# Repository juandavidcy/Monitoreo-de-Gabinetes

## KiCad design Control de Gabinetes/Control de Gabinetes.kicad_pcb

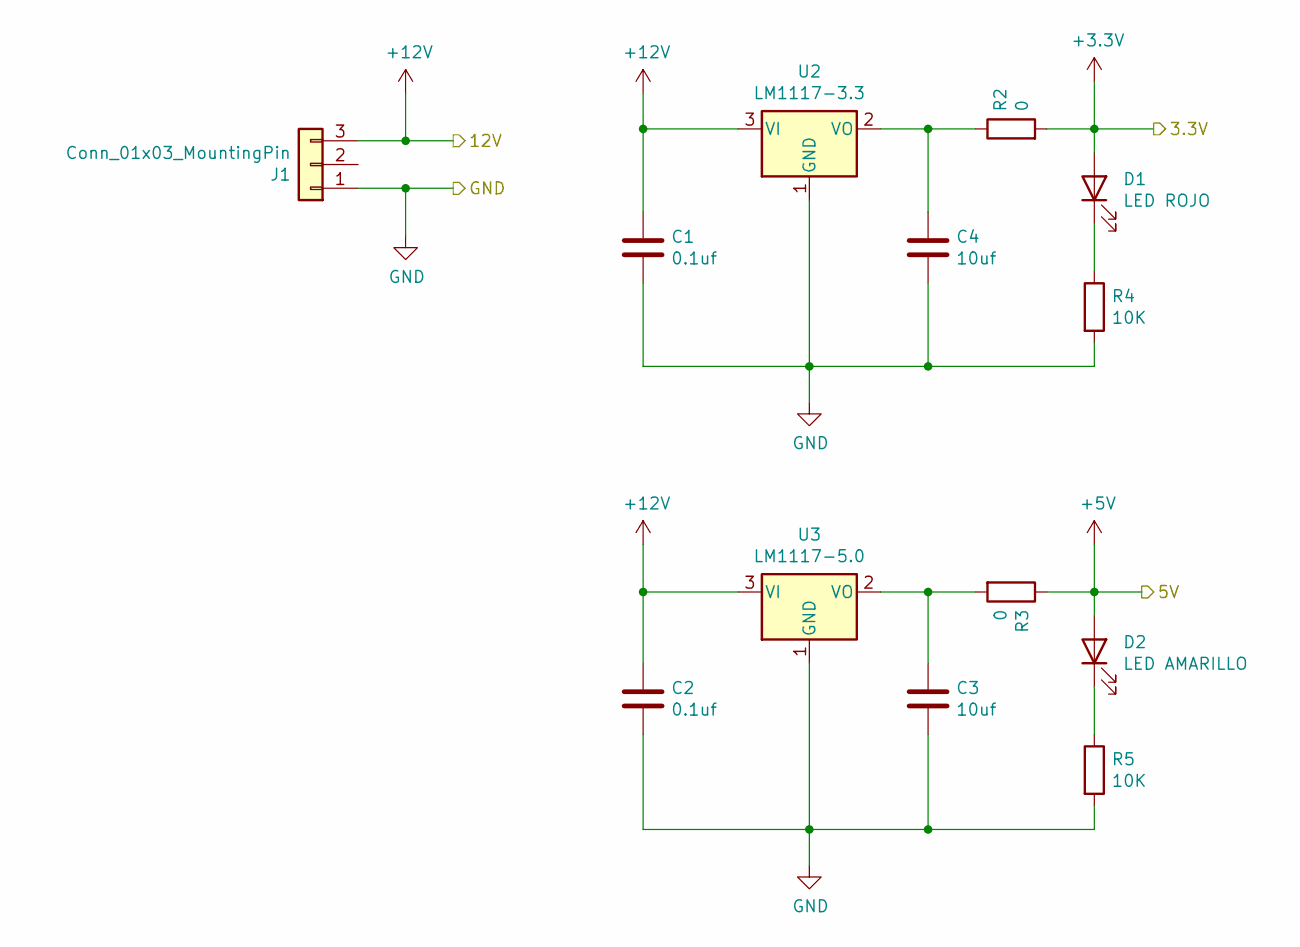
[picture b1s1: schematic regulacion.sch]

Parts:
C1, C2: 0.1uf; C_0805_2012Metric
C3, C4: 10uf; C_0805_2012Metric
D1: LED ROJO; LED_0805_2012Metric
D2: LED AMARILLO; LED_0805_2012Metric
J1: Conn_01x03_MountingPin; Molex_KK-254_AE-6410-03A_1x03_P2.54mm_Vertical
R2, R3: 0; R_0805_2012Metric
R4, R5: 10K; R_0805_2012Metric
U2: LM1117-3.3; SOT-223-3_TabPin2
U3: LM1117-5.0; SOT-223-3_TabPin2

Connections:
+3V3: D1.2 (A), R2.2; also elsewhere on the board
+5V: D2.2 (A), R3.1; also elsewhere on the board
+12V: C1.1, C2.1, J1.3, U2.3 (VI), U3.3 (VI)
GND: C1.2, C2.2, C3.2, C4.2, J1.1, R4.2, R5.2, U2.1 (GND), U3.1 (GND); also elsewhere on the board
unnamed: C3.1, R3.2, U3.2 (VO)
unnamed: C4.1, R2.1, U2.2 (VO)
unnamed: D1.1 (K), R4.1
unnamed: D2.1 (K), R5.1

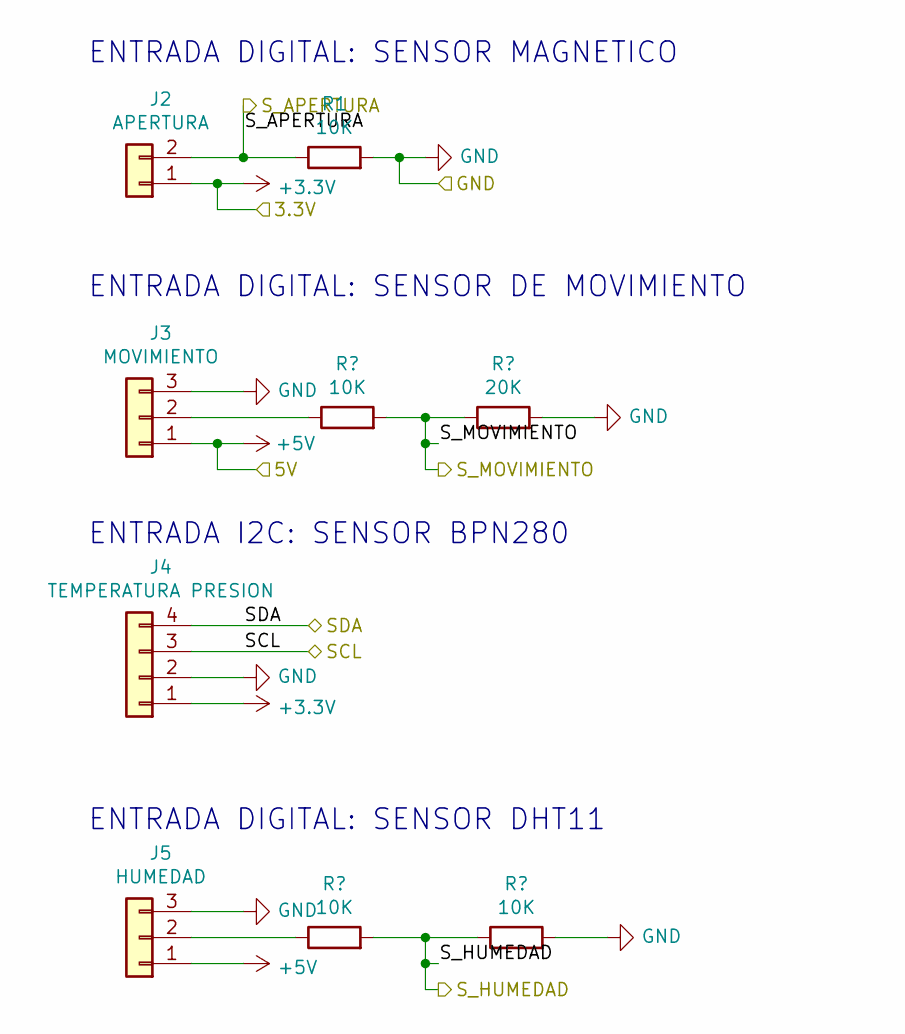
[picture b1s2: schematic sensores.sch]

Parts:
J2: APERTURA; Molex_KK-254_AE-6410-02A_1x02_P2.54mm_Vertical
J3: MOVIMIENTO; Molex_KK-254_AE-6410-03A_1x03_P2.54mm_Vertical
J4: TEMPERATURA PRESION; Molex_KK-254_AE-6410-04A_1x04_P2.54mm_Vertical
J5: HUMEDAD; Molex_KK-254_AE-6410-03A_1x03_P2.54mm_Vertical
R1: 10K; R_0805_2012Metric

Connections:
+3V3: J2.1, J4.1; also elsewhere on the board
+5V: J3.1, J5.1; also elsewhere on the board
/SCL: J4.3; also elsewhere on the board
/SDA: J4.4; also elsewhere on the board
/S_APERTURA: J2.2, R1.1; also elsewhere on the board
GND: J3.3, J4.2, J5.3, R1.2; also elsewhere on the board
unnamed 47: J3.2; also elsewhere on the board
unnamed 48: J5.2; also elsewhere on the board

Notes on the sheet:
ENTRADA DIGITAL: SENSOR MAGNETICO
ENTRADA DIGITAL: SENSOR DE MOVIMIENTO
ENTRADA I2C: SENSOR BPN280
ENTRADA DIGITAL: SENSOR DHT11

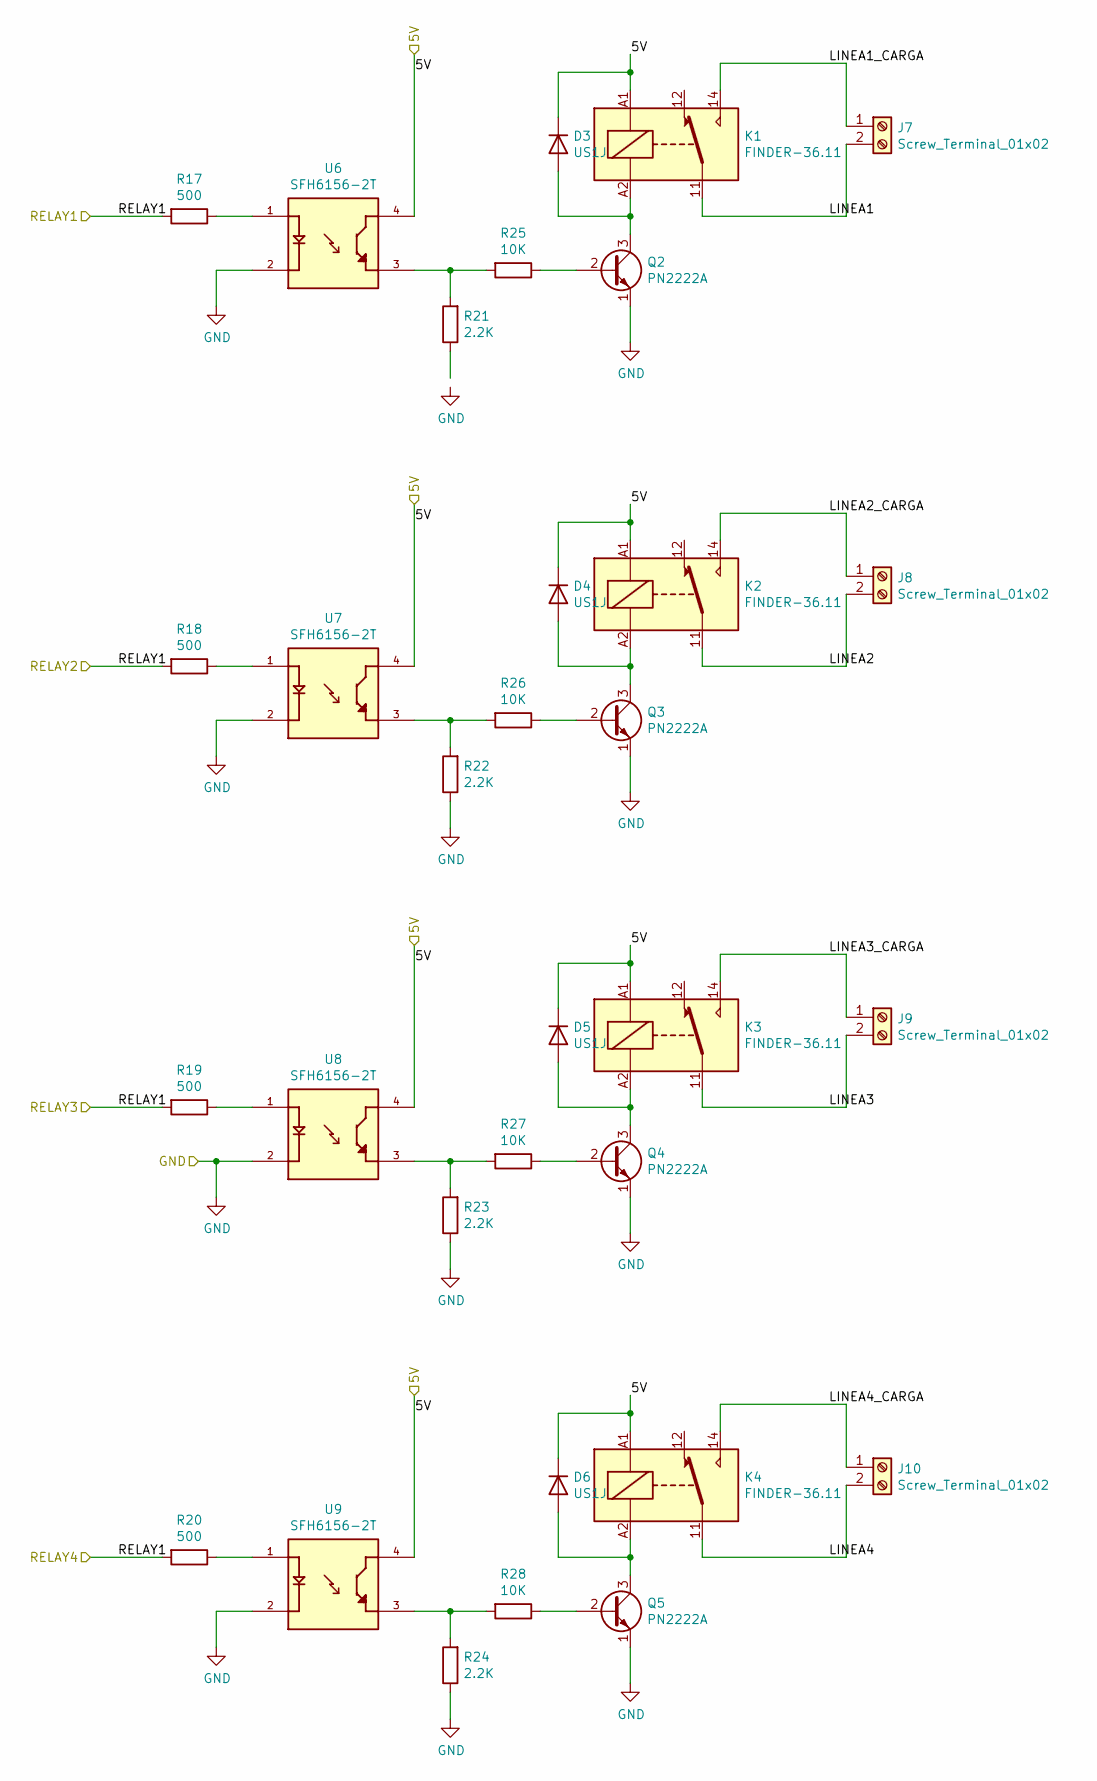
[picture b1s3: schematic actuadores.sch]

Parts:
D3, D4, D5, D6: US1J; D_SMA
J7, J8, J9, J10: Screw_Terminal_01x02; TerminalBlock_bornier-2_P5.08mm
K1, K2, K3, K4: FINDER-36.11; Relay_SPDT_Finder_36.11
Q2, Q3, Q4, Q5: PN2222A; TO-92_Inline
R17, R18, R19, R20: 500; R_0805_2012Metric
R21, R22, R23, R24: 2.2K; R_0805_2012Metric
R25, R26, R27, R28: 10K; R_0805_2012Metric
U6, U7, U8, U9: SFH6156-2T; SOT254P978X405-4N; DIGI-KEY_PART_NUMBER 751-1346-1-ND

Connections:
+5V: D3.1 (K), D4.1 (K), D5.1 (K), D6.1 (K), K1.A1, K2.A1, K3.A1, K4.A1, U6.4, U7.4, U8.4, U9.4; also elsewhere on the board
/actuadores/LINEA1: J7.2, K1.11
/actuadores/LINEA1_CARGA: J7.1, K1.14
/actuadores/LINEA2: J8.2, K2.11
/actuadores/LINEA2_CARGA: J8.1, K2.14
/actuadores/LINEA3: J9.2, K3.11
/actuadores/LINEA3_CARGA: J9.1, K3.14
/actuadores/LINEA4: J10.2, K4.11
/actuadores/LINEA4_CARGA: J10.1, K4.14
GND: Q2.1 (E), Q3.1 (E), Q4.1 (E), Q5.1 (E), R21.1, R22.1, R23.1, R24.1, U6.2, U7.2, U8.2, U9.2; also elsewhere on the board
unnamed: D3.2 (A), K1.A2, Q2.3 (C)
unnamed: D4.2 (A), K2.A2, Q3.3 (C)
unnamed: D5.2 (A), K3.A2, Q4.3 (C)
unnamed: D6.2 (A), K4.A2, Q5.3 (C)
unnamed: Q2.2 (B), R25.1
unnamed: Q3.2 (B), R26.1
unnamed: Q4.2 (B), R27.1
unnamed: Q5.2 (B), R28.1
unnamed: R17.1, U6.1
unnamed: R18.1, U7.1
unnamed: R19.1, U8.1
unnamed: R20.1, U9.1
unnamed: R21.2, R25.2, U6.3
unnamed: R22.2, R26.2, U7.3
unnamed: R23.2, R27.2, U8.3
unnamed: R24.2, R28.2, U9.3

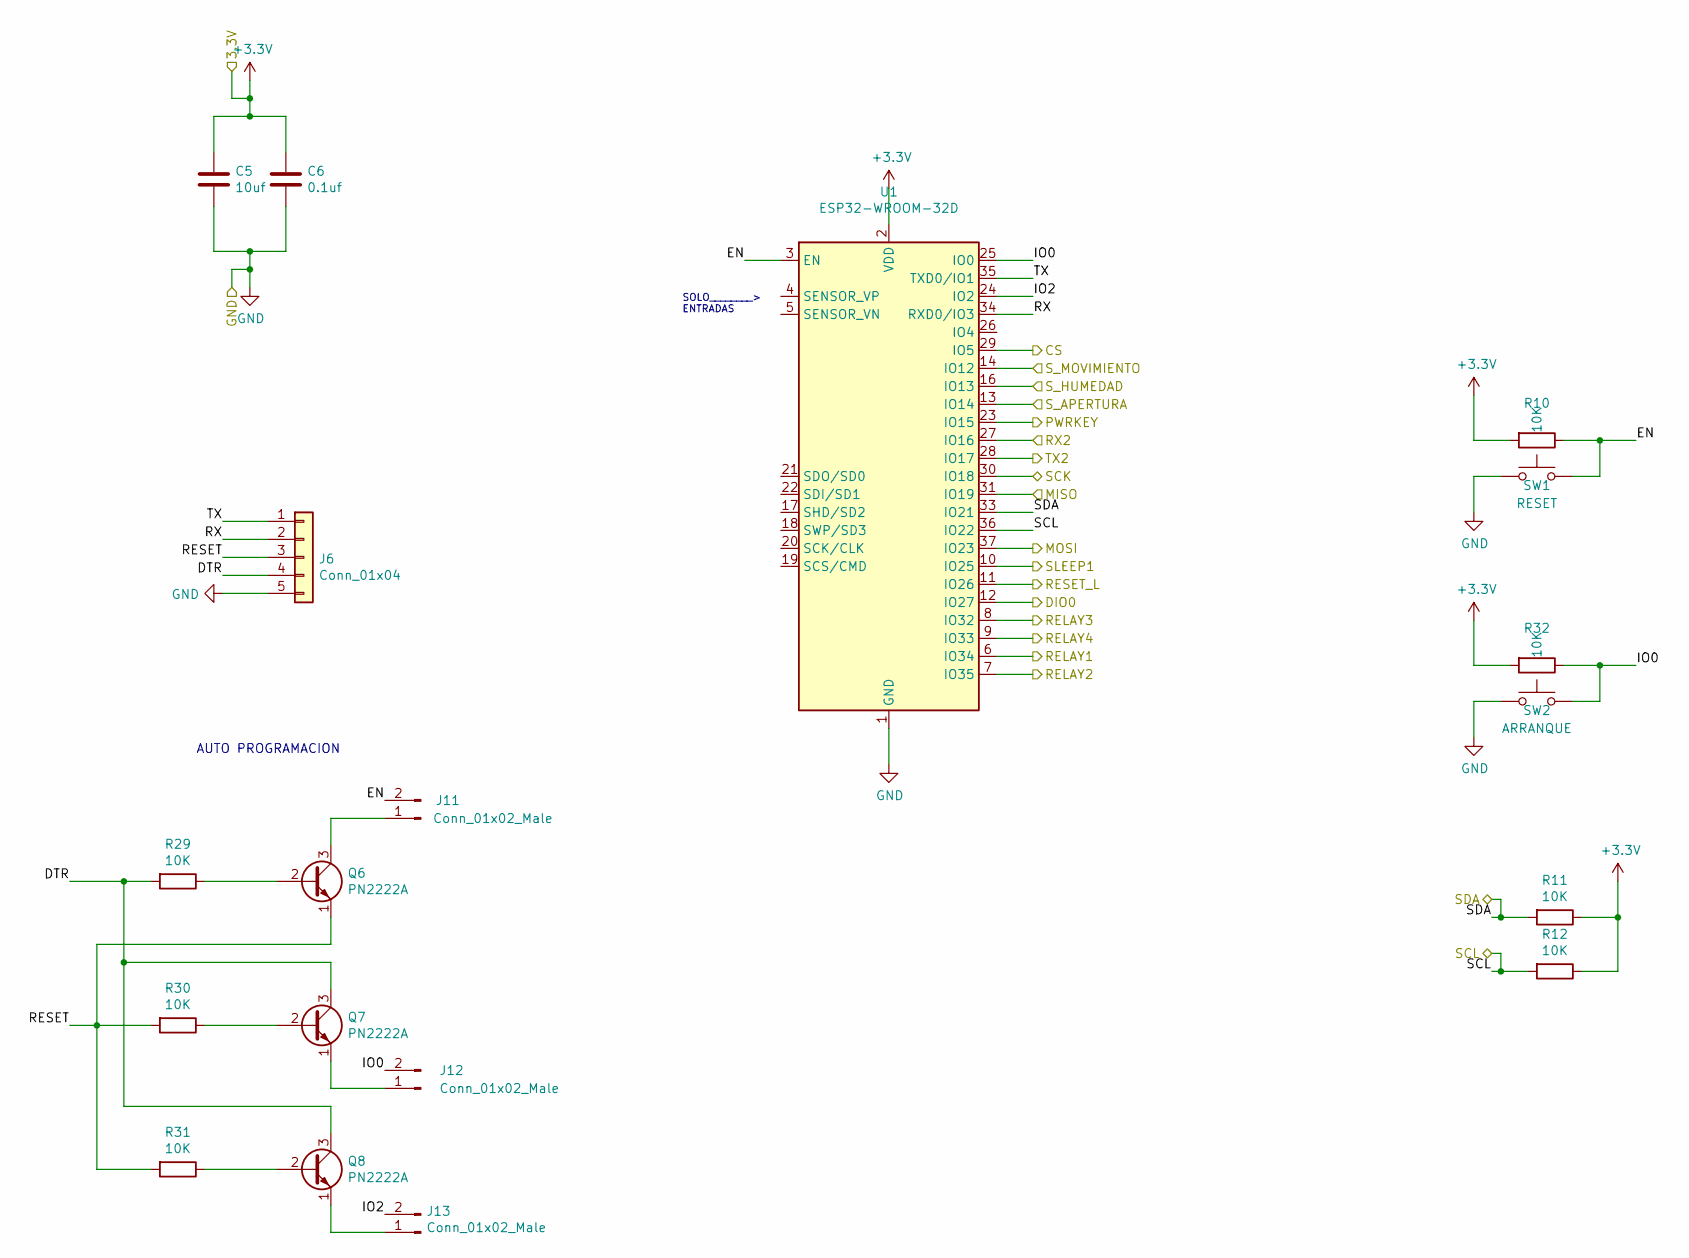
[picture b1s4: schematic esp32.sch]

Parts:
C5: 10uf; C_0805_2012Metric
C6: 0.1uf; C_0805_2012Metric
J6: Conn_01x04; Molex_KK-254_AE-6410-05A_1x05_P2.54mm_Vertical
J11, J12, J13: Conn_01x02_Male; PinHeader_1x02_P2.54mm_Vertical
Q6, Q7, Q8: PN2222A; SOT-23
R10, R11, R12, R29, R30, R31, R32: 10K; R_0805_2012Metric
SW1: RESET; SW_SPST_TL3342
SW2: ARRANQUE; SW_SPST_TL3342
U1: ESP32-WROOM-32D; ESP32-WROOM-32U

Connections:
+3V3: C5.2, C6.1, R10.2, R11.1, R12.1, R32.2, U1.2 (VDD); also elsewhere on the board
/CS: U1.29 (IO5); also elsewhere on the board
/DIO0: U1.13 (IO14); also elsewhere on the board
/MISO: U1.31 (IO19); also elsewhere on the board
/MOSI: U1.37 (IO23); also elsewhere on the board
/PWRKEY: U1.16 (IO13); also elsewhere on the board
/RESET_L: U1.14 (IO12); also elsewhere on the board
/RX2: U1.27 (IO16); also elsewhere on the board
/SCK: U1.30 (IO18); also elsewhere on the board
/SCL: R12.2, U1.36 (IO22); also elsewhere on the board
/SDA: R11.2, U1.33 (IO21); also elsewhere on the board
/SLEEP1: U1.23 (IO15); also elsewhere on the board
/S_APERTURA: U1.12 (IO27); also elsewhere on the board
/S_HUMEDAD: U1.11 (IO26); also elsewhere on the board
/S_MOVIMIENTO: U1.10 (IO25); also elsewhere on the board
/TX2: U1.28 (IO17); also elsewhere on the board
/esp32/DTR: J6.4, Q7.3 (C), Q8.3 (C), R29.2
/esp32/EN: J11.2, R10.1, SW1.2, U1.3 (EN); also elsewhere on the board
/esp32/IO0: J12.2, R32.1, SW2.2, U1.25 (IO0); also elsewhere on the board
/esp32/IO2: J13.2, U1.24 (IO2)
/esp32/RESET: J6.3, Q6.1 (E), R30.2, R31.2
/esp32/RX: J6.2, U1.34 (RXD0/IO3)
/esp32/TX: J6.1, U1.35 (TXD0/IO1)
GND: C5.1, C6.2, J6.5, SW1.1, SW2.1, U1.1 (GND), U1.15 (GND), U1.38 (GND), U1.39 (GND); also elsewhere on the board
unnamed: J11.1, Q6.3 (C)
unnamed: J12.1, Q7.1 (E)
unnamed: J13.1, Q8.1 (E)
unnamed: Q6.2 (B), R29.1
unnamed: Q7.2 (B), R30.1
unnamed: Q8.2 (B), R31.1

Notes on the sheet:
SOLO________> ENTRADAS
AUTO PROGRAMACION

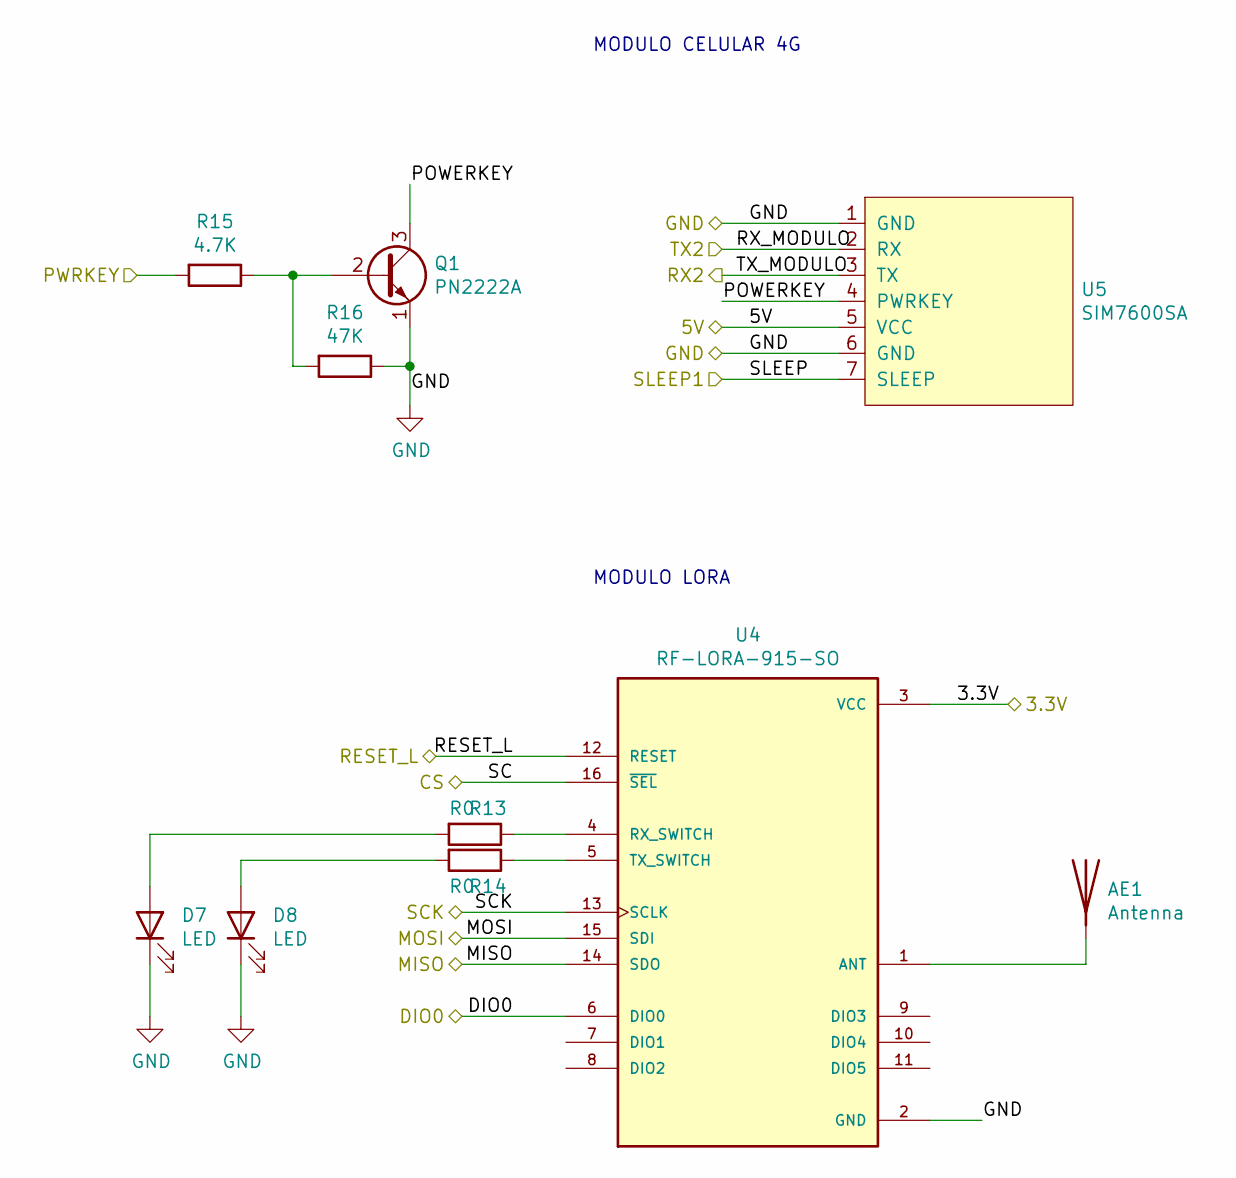
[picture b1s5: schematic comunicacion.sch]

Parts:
AE1: Antenna; Texas_SWRA416_868MHz_915MHz
D7, D8: LED; LED_0805_2012Metric
Q1: PN2222A; SOT-23
R13, R14: R0; R_0805_2012Metric
R15: 4.7K; R_0805_2012Metric
R16: 47K; R_0805_2012Metric
U4: RF-LORA-915-SO; XCVR_RF-LORA-868-SO
U5: SIM7600SA

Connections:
+3V3: U4.3 (VCC); also elsewhere on the board
+5V: U5.5 (VCC); also elsewhere on the board
/CS: U4.16 (~SEL); also elsewhere on the board
/DIO0: U4.6 (DIO0); also elsewhere on the board
/MISO: U4.14 (SDO); also elsewhere on the board
/MOSI: U4.15 (SDI); also elsewhere on the board
/PWRKEY: R15.2; also elsewhere on the board
/RESET_L: U4.12 (RESET); also elsewhere on the board
/RX2: U5.3 (TX); also elsewhere on the board
/SCK: U4.13 (SCLK); also elsewhere on the board
/SLEEP1: U5.7 (SLEEP); also elsewhere on the board
/TX2: U5.2 (RX); also elsewhere on the board
/comunicacion/ANT: AE1.1, U4.1 (ANT)
/comunicacion/POWERKEY: Q1.3 (C), U5.4 (PWRKEY)
GND: D7.1 (K), D8.1 (K), Q1.1 (E), R16.1, U4.2 (GND), U5.1 (GND), U5.6 (GND); also elsewhere on the board
unnamed: D7.2 (A), R13.2
unnamed: D8.2 (A), R14.2
unnamed: Q1.2 (B), R15.1, R16.2
unnamed: R13.1, U4.4 (RX_SWITCH)
unnamed: R14.1, U4.5 (TX_SWITCH)

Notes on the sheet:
MODULO CELULAR 4G
MODULO LORA

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
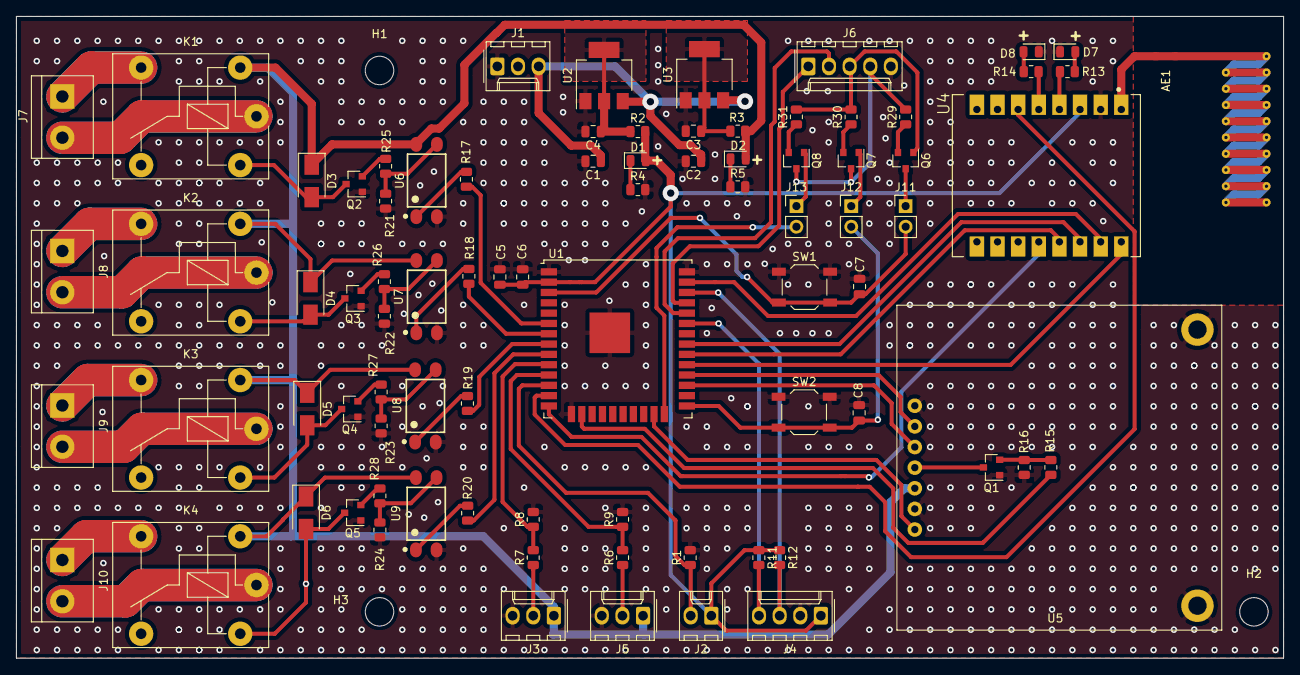
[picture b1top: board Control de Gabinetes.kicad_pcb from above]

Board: 2 copper layers, 156.0 x 79.0 mm, 86 parts (0 on the bottom side), 73 nets.

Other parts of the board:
C7, C8: 0.1uf; C_0805_2012Metric
H1, H2, H3: MountingHole; MountingHole_3.5mm
R6, R7, R9: 10K; R_0805_2012Metric
R8: 20K; R_0805_2012Metric

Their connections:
/S_HUMEDAD: R6.2, R9.1; also elsewhere on the board
/S_MOVIMIENTO: R7.2, R8.1; also elsewhere on the board
/esp32/EN: C7.2; also elsewhere on the board
/esp32/IO0: C8.1; also elsewhere on the board
GND: C7.1, C8.2, R8.2, R9.2; also elsewhere on the board
unnamed 47: R7.1; also elsewhere on the board
unnamed 48: R6.1; also elsewhere on the board

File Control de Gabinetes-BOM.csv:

"Id";"Identificador";"Empaquetado";"Cantidad";"Identificación";"Suministrador y ref";
1;"U9,U8,U7,U6";"SOT254P978X405-4N";4;"SFH6156-2T";;;
2;"AE1";"Texas_SWRA416_868MHz_915MHz";1;"Antenna";;;
3;"H3,H2,H1";"MountingHole_3.5mm";3;"MountingHole";;;
4;"J10,J9,J8,J7";"TerminalBlock_bornier-2_P5.08mm";4;"Screw_Terminal_01x02";;;
5;"U5";"SIM7600SA";1;"SIM7600SA";;;
6;"K1,K3,K4,K2";"Relay_SPDT_Finder_36.11";4;"FINDER-36.11";;;
7;"U4";"XCVR_RF-LORA-868-SO";1;"RF-LORA-915-SO";;;
8;"C8,C7,C6,C2,C1";"C_0805_2012Metric";5;"0.1uf";;;
9;"D3,D6,D5,D4";"D_SMA";4;"US1J";;;
10;"Q2,Q8,Q7,Q6,Q5,Q4,Q3,Q1";"SOT-23";8;"PN2222A";;;
11;"R25,R31,R30,R29,R28,R27,R26,R12,R11,R9,R7,R6,R5,R4,R1";"R_0805_2012Metric";15;"10K";;;
12;"R21,R24,R23,R22";"R_0805_2012Metric";4;"2.2K";;;
13;"U1";"ESP32-WROOM-32U";1;"ESP32-WROOM-32D";;;
14;"D8,D7";"LED_0805_2012Metric";2;"LED";;;
15;"J6";"Molex_KK-254_AE-6410-05A_1x05_P2.54mm_Vertical";1;"Conn_01x04";;;
16;"J13,J12,J11";"PinHeader_1x02_P2.54mm_Vertical";3;"Conn_01x02_Male";;;
17;"SW2";"SW_SPST_TL3342";1;"ARRANQUE";;;
18;"R20,R19,R18,R17";"R_0805_2012Metric";4;"500";;;
19;"R16";"R_0805_2012Metric";1;"47K";;;
20;"R15";"R_0805_2012Metric";1;"4.7K";;;
21;"R14,R13";"R_0805_2012Metric";2;"R0";;;
22;"SW1";"SW_SPST_TL3342";1;"RESET";;;
23;"R8";"R_0805_2012Metric";1;"20K";;;
24;"R3,R2";"R_0805_2012Metric";2;"0";;;
25;"D2";"LED_0805_2012Metric";1;"LED AMARILLO";;;
26;"D1";"LED_0805_2012Metric";1;"LED ROJO";;;
27;"C5,C4,C3";"C_0805_2012Metric";3;"10uf";;;
28;"U3";"SOT-223-3_TabPin2";1;"LM1117-5.0";;;
29;"U2";"SOT-223-3_TabPin2";1;"LM1117-3.3";;;
30;"J5";"Molex_KK-254_AE-6410-03A_1x03_P2.54mm_Vertical";1;"HUMEDAD";;;
31;"J4";"Molex_KK-254_AE-6410-04A_1x04_P2.54mm_Vertical";1;"TEMPERATURA PRESION";;;
32;"J3";"Molex_KK-254_AE-6410-03A_1x03_P2.54mm_Vertical";1;"MOVIMIENTO";;;
33;"J2";"Molex_KK-254_AE-6410-02A_1x02_P2.54mm_Vertical";1;"APERTURA";;;
34;"J1";"Molex_KK-254_AE-6410-03A_1x03_P2.54mm_Vertical";1;"Conn_01x03_MountingPin";;;

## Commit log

2021-05-12 avance1
    Arquitectura del sitema.
    Iinicializando proyecto en kidcad, se crean las hojas de trabajo correspondiente, se agregan los reguladores de voltaje y se agregan los sensores
2021-07-01 Avance 1/07/2021
2021-07-06 avance 6/07
2021-07-08 AVANCE 7/7/2021
2021-07-13 AVANCE 13/07/2021
2021-07-19 avance 19/07
2021-07-20 avance2 19/07/2021
2021-07-21 avance 20/07/2021
2021-07-29 avance 28/07/2021
